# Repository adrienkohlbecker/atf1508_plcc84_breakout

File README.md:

# ATF1508 Breakout

Breakout board for Atmel's AFT1508 CPLDs in a through-hole PLCC-84 socket. The size is friendly for breadboard use, with two rows of holes left available on each side of the breadboard for wires to come in.

## Board

## Schematic

## BOM

| Refs | Qty | Component | Description |
| ----- | --- | ---- | ----------- |
| C1 | 1 | 10u | Polarized capacitor, through hole D4.0mm P1.5mm |
| C2, C3, C4, C5, C6, C7, C8, C9 | 8 | 100n | Unpolarized capacitor, 0805 SMD |
| J1 | 1 | Atmel-JTAG-10 | Atmel 10-pin JTAG connector, 2x5 IDC |
| J2, J3 | 2 | Conn_01x35 | Generic connector, single row, 01x35 |
| U1 | 1 | ATF1508AS-xJx84 | Microchip CPLD, in PLCC-84 through-hole socket |

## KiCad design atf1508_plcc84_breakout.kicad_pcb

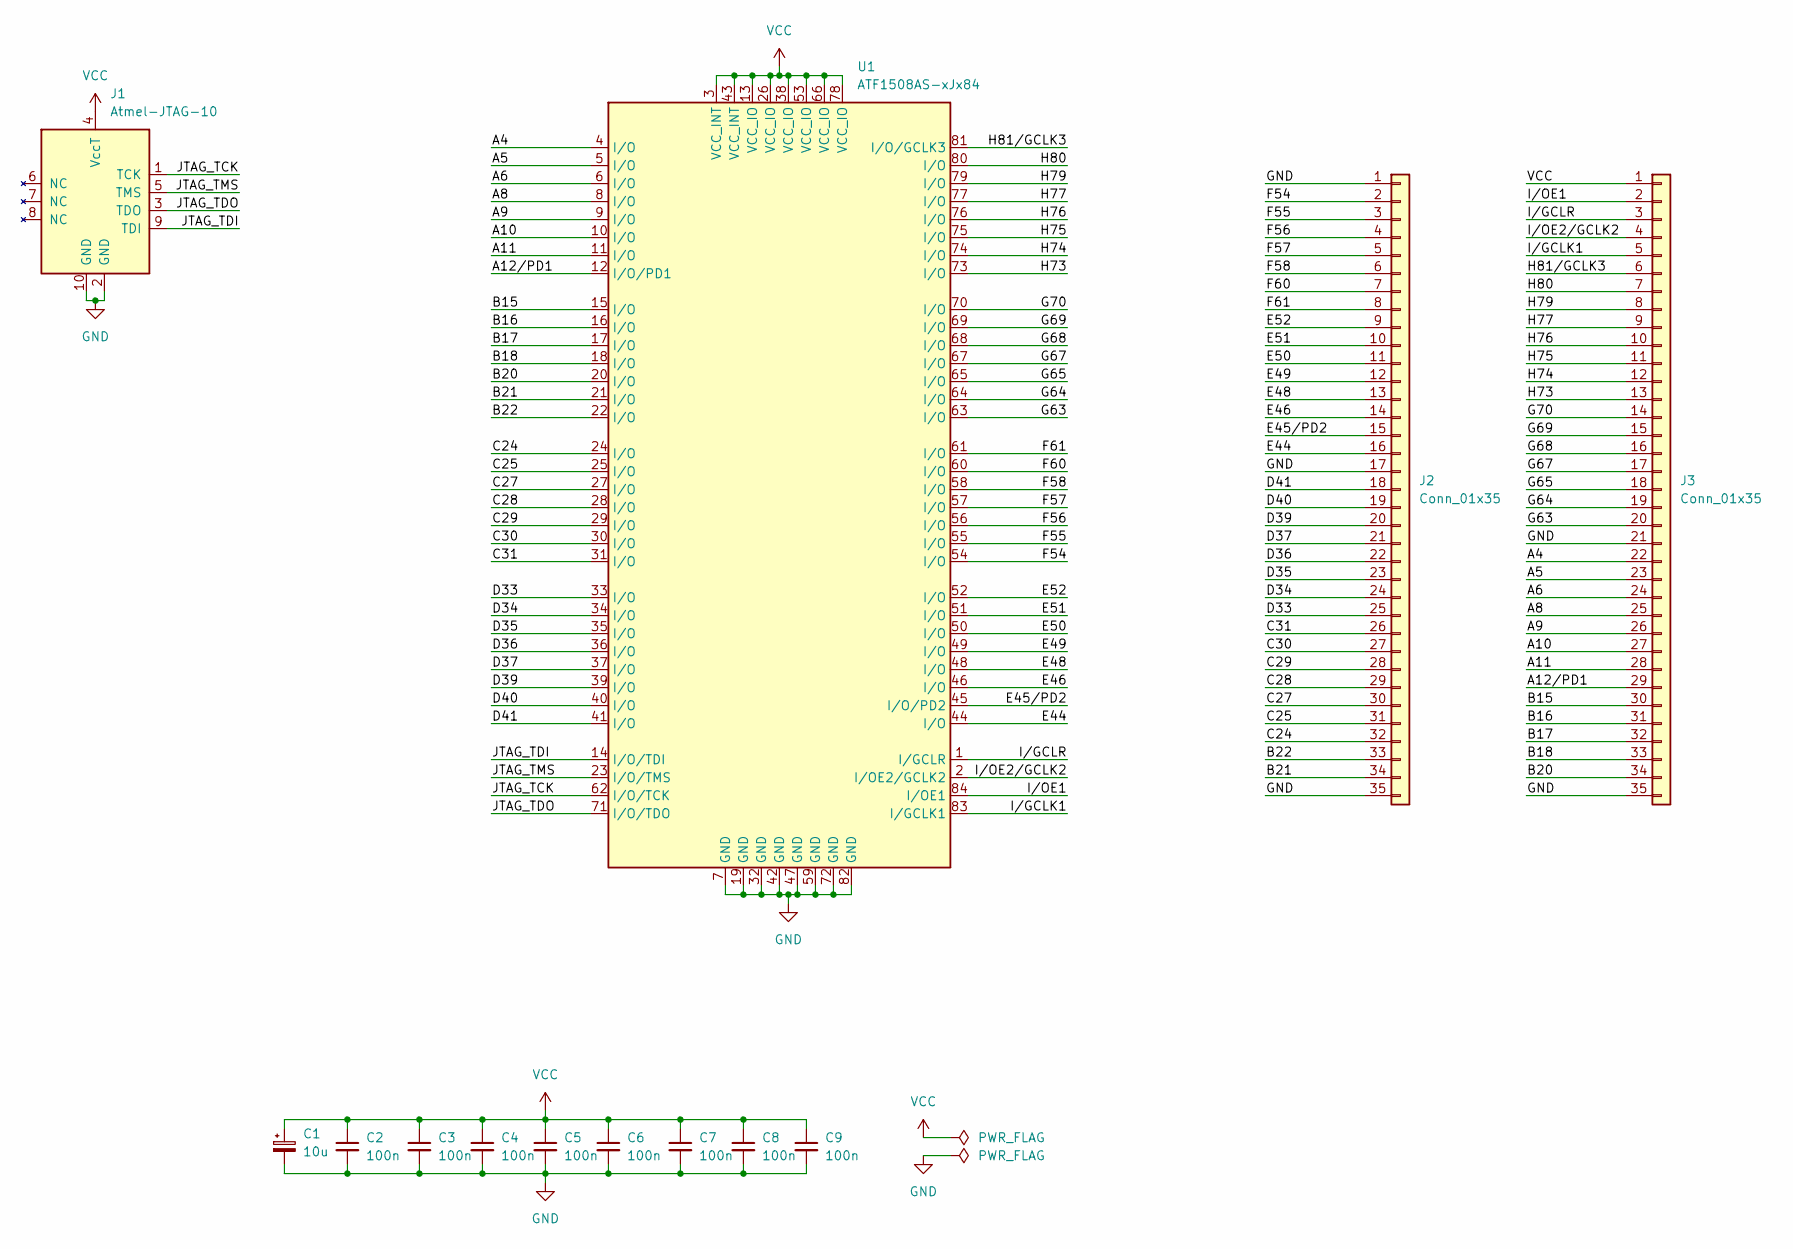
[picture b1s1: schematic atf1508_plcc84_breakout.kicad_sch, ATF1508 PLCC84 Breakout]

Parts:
C1: 10u; CP_Radial_D4.0mm_P1.50mm
C2, C3, C4, C5, C6, C7, C8, C9: 100n; C_0805_2012Metric_Pad1.18x1.45mm_HandSolder
J1: Atmel-JTAG-10; IDC-Header_2x05_P2.54mm_Vertical
J2, J3: Conn_01x35; PinHeader_1x35_P2.54mm_Vertical
U1: ATF1508AS-xJx84; PLCC-84_THT-Socket

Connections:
/A4: J3.22, U1.4 (I/O)
/A5: J3.23, U1.5 (I/O)
/A6: J3.24, U1.6 (I/O)
/A8: J3.25, U1.8 (I/O)
/A9: J3.26, U1.9 (I/O)
/A10: J3.27, U1.10 (I/O)
/A11: J3.28, U1.11 (I/O)
/A12/PD1: J3.29, U1.12 (I/O/PD1)
/B15: J3.30, U1.15 (I/O)
/B16: J3.31, U1.16 (I/O)
/B17: J3.32, U1.17 (I/O)
/B18: J3.33, U1.18 (I/O)
/B20: J3.34, U1.20 (I/O)
/B21: J2.34, U1.21 (I/O)
/B22: J2.33, U1.22 (I/O)
/C24: J2.32, U1.24 (I/O)
/C25: J2.31, U1.25 (I/O)
/C27: J2.30, U1.27 (I/O)
/C28: J2.29, U1.28 (I/O)
/C29: J2.28, U1.29 (I/O)
/C30: J2.27, U1.30 (I/O)
/C31: J2.26, U1.31 (I/O)
/D33: J2.25, U1.33 (I/O)
/D34: J2.24, U1.34 (I/O)
/D35: J2.23, U1.35 (I/O)
/D36: J2.22, U1.36 (I/O)
/D37: J2.21, U1.37 (I/O)
/D39: J2.20, U1.39 (I/O)
/D40: J2.19, U1.40 (I/O)
/D41: J2.18, U1.41 (I/O)
/E44: J2.16, U1.44 (I/O)
/E45/PD2: J2.15, U1.45 (I/O/PD2)
/E46: J2.14, U1.46 (I/O)
/E48: J2.13, U1.48 (I/O)
/E49: J2.12, U1.49 (I/O)
/E50: J2.11, U1.50 (I/O)
/E51: J2.10, U1.51 (I/O)
/E52: J2.9, U1.52 (I/O)
/F54: J2.2, U1.54 (I/O)
/F55: J2.3, U1.55 (I/O)
/F56: J2.4, U1.56 (I/O)
/F57: J2.5, U1.57 (I/O)
/F58: J2.6, U1.58 (I/O)
/F60: J2.7, U1.60 (I/O)
/F61: J2.8, U1.61 (I/O)
/G63: J3.20, U1.63 (I/O)
/G64: J3.19, U1.64 (I/O)
/G65: J3.18, U1.65 (I/O)
/G67: J3.17, U1.67 (I/O)
/G68: J3.16, U1.68 (I/O)
/G69: J3.15, U1.69 (I/O)
/G70: J3.14, U1.70 (I/O)
/H73: J3.13, U1.73 (I/O)
/H74: J3.12, U1.74 (I/O)
/H75: J3.11, U1.75 (I/O)
/H76: J3.10, U1.76 (I/O)
/H77: J3.9, U1.77 (I/O)
/H79: J3.8, U1.79 (I/O)
/H80: J3.7, U1.80 (I/O)
/H81/GCLK3: J3.6, U1.81 (I/O/GCLK3)
/I/GCLK1: J3.5, U1.83 (I/GCLK1)
/I/GCLR: J3.3, U1.1 (I/GCLR)
/I/OE1: J3.2, U1.84 (I/OE1)
/I/OE2/GCLK2: J3.4, U1.2 (I/OE2/GCLK2)
/JTAG_TCK: J1.1 (TCK), U1.62 (I/O/TCK)
/JTAG_TDI: J1.9 (TDI), U1.14 (I/O/TDI)
/JTAG_TDO: J1.3 (TDO), U1.71 (I/O/TDO)
/JTAG_TMS: J1.5 (TMS), U1.23 (I/O/TMS)
GND: C1.2, C2.2, C3.2, C4.2, C5.2, C6.2, C7.2, C8.2, C9.2, J1.2 (GND), J1.10 (GND), J2.1, J2.17, J2.35, J3.21, J3.35, U1.7 (GND), U1.19 (GND), U1.32 (GND), U1.42 (GND), U1.47 (GND), U1.59 (GND), U1.72 (GND), U1.82 (GND); also elsewhere on the board
VCC: C1.1, C2.1, C3.1, C4.1, C5.1, C6.1, C7.1, C8.1, C9.1, J1.4 (VccT), J3.1, U1.3 (VCC_INT), U1.13 (VCC_IO), U1.26 (VCC_IO), U1.38 (VCC_IO), U1.43 (VCC_INT), U1.53 (VCC_IO), U1.66 (VCC_IO), U1.78 (VCC_IO); also elsewhere on the board

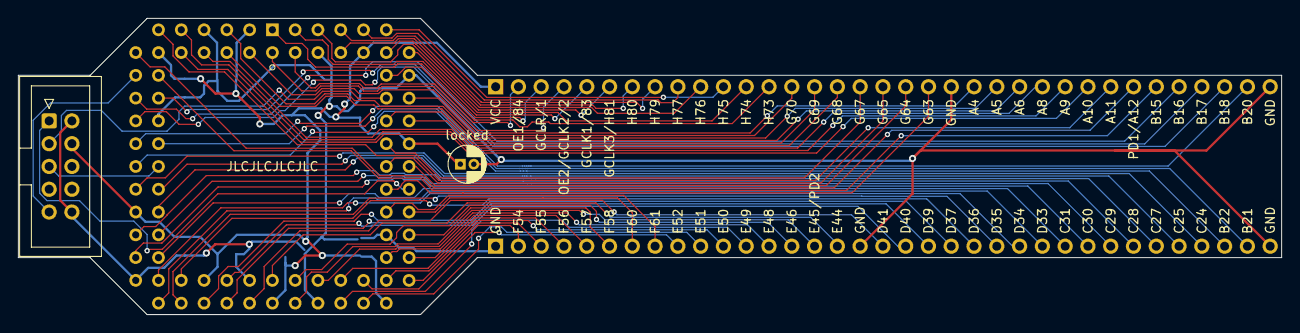
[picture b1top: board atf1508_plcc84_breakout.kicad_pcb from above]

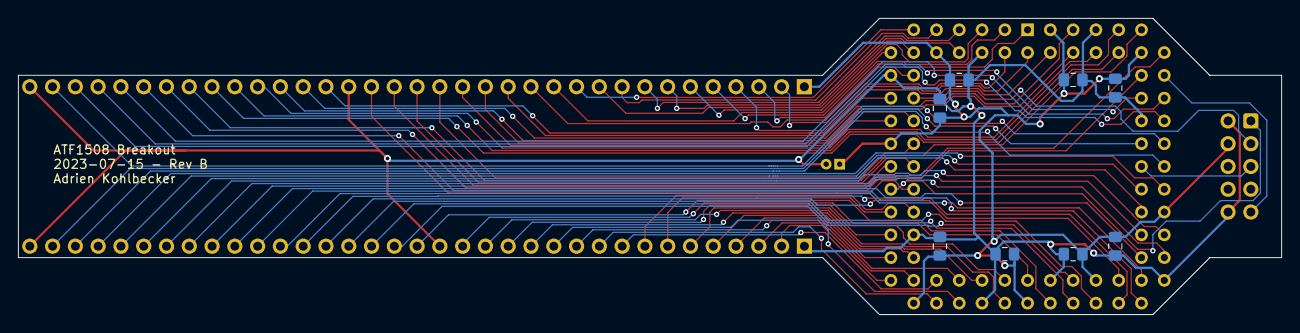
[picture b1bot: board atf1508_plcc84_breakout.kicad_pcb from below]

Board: 2 copper layers, 140.8 x 33.0 mm, 13 parts (10 on the bottom side), 70 nets.

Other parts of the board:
locked: 10u; CP_Radial_D4.0mm_P1.50mm

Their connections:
GND: locked.2; also elsewhere on the board
VCC: locked.1; also elsewhere on the board

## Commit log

2023-06-20 First release
2023-07-03 Revert oscillator addition
2023-07-15 Add pin numbers for global inputs and re-order them
2023-07-19 Re-add RevA

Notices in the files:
atf1508_plcc84_breakout.kicad_pcb:
Licensed under CERN-OHL-W v2
Copyright © Adrien Kohlbecker
